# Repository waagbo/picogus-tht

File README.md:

# PicoGUS THT

PicoGUS is a Raspberry Pi Pico based ISA sound card for DOS and Win9x retro computers.
It is a highly versatile clone card that provides near perfect emulation of the Gravis Ultrasound, Sound Blaster-series, AdLib, Tandy 3-voice and CMS/Game Blaster.

Additional features like CD-ROM (Panasonic MKE), MPU-401 and USB game controllers build further on the cards versatility and the wavetable header will further extend the capacity with a card like [X2GS from Serdaco](https://serdashop.com/products/x2gs-te) to get the original Roland magic or even a [WavetablePi](https://github.com/scrapcomputing/WavetablePiHoriz) for the ultimate all-in-one experience for MS-DOS games. 

**PicoGUS THT is a through-hole conversion of the [PicoGUS project](https://github.com/polpo/picogus).**<br />
The conversion introduces through-hole components where possible in addition to embedding new features and ideas while still keeping the card compatible with the upstream project. The design goal is to make the project be easier to solder by hand as well as giving it a higher level of retro asthetics.

PicoGUS THT exists in multiple variants based on different PicoGUS revisions. Each variant is found in their separate folder (or branch if still experimental). The different *hw* designs feature additional documentation including ready to order BOM CSVs in their respective *docs* folders.

The designs still have some TSSOP SMD chips as they do not have THT equivalents, namely the two *SN74CB3T3257PWR* level shifters (U3/U4) as well as the PCM510xA DAC. PicoGUS THT features a redesigned footprint to ease debugging in case something goes wrong.

**Note!** The hardware revisions are intentionally kept aligned with the *major* revision as the original PicoGUS boards. This is done to indicate hardware feature compatibility and to prevent confusion in case of any future major revisions of the original PicoGUS design.

### Version 1.3

This version is an extension of the PicoGUS 1.2 design while implementing the *wavetable header* with manual volume control from the *hw-hand386* branch. Together with the addition of a full size USB-A connector accessible from the computers backside this card is now a real competitor to the v2.0 SMD design.

In addition, the THT boards have also been slightly resized to optimize for component placement and JCLPCB-pricing.
The v1.3.2 is currently under quality assurance. The following features have been tested and verified.
* [x] Card Assembly ➔ Minor adjustments to DigiKey BOM.
* [x] Flash, boot and detect card ➔ OK (v4.2.0-beta2).
* [x] Audio Playback ➔ OK (v4.2.0-beta2, SB Mode).
* [x] Wavetable MIDI Playback  ➔ OK (WavetablePi)
* [ ] External MIDI Playback
* [x] USB-A Connector (Both CD-ROM and experimental PGDFS filesystem)

The release version v1.3.2 is still pending build/test.

Assembly should be *EASY to MEDIUM* with the appropriate quality tools and consumables and a good project for beginners that want a little more challenge. Here is a list of recommended supplies with some personal recommendations:
* [Low Temperature Solder Paste](https://www.digikey.com/en/products/detail/chip-quik-inc/NC191LTA10/13531404) for easy soldering of SMD components.
* [Flux](https://www.digikey.com/en/products/detail/chip-quik-inc/NC191-2CC6/11480375) as it makes solder behave like magic when you need it the most.
* [Solder Wick](https://www.digikey.com/en/products/detail/chemtronics/SW14035/5177685) as it will help you when flux can't. Remember to **NEVER** pull a stuck wick.
* [Soldering Iron with J-Tip (Alientek T90B)](https://www.aliexpress.com/item/1005010015046346.html) will make the SMD components a breeze to solder. 
* [Tweezers](https://www.aliexpress.com/item/1005007298021096.html) for handling the SMD components.
* Digital Microscope of decent quality from AliExpress is very useful for visual inspection of SMD chips.
* Multimeter with good continuity tester.

### Version 2.1

This is an experimental extension of the PicoGUS 2.0 SMD design, made possible using a Waveshare Core2350B board to free enough I/O ports for the 2.0 feature set. This is still in the design phase.
<br/>

### Experimental Firmware
We have added experimental features that adds upon community ideas on top of the original firmware and software components. The features are submitted as Pull Requests to the original PicoGUS repository as well but there is no guarantee that they will ever be included in the official software releases:
* DFS drive support inspired by PicoMEM so the USB drive can be accessed from MS-DOS.
* CD images in a `CDROM` folder on the USB drive.
* A web page on boards with a Pico W or Pico 2 W: status, volumes, settings, mode switching, mt32-pi control and firmware updates from a browser.

The experimental features live on their own branches and are built into a separate *experimental* set of firmware and DOS tools next to the regular one, see [sw/experimental](sw/experimental/README.md).

### RP2350 Firmware
The firmware builds for the RP2350 as well as the RP2040, from the same source: for the v1.x boards with a Raspberry Pi Pico 2 (W) instead of a Pico (W), and for the v2.1 board's Core2350B module. Releases contain the firmware for both microcontrollers. See [RP2350 support](sw/docs/rp2350.md) for the firmware files, how to build them and what is left to test on hardware.

<br/>

**A big thank you to [Ian Scott (polpo)](https://github.com/polpo/) for the PicoGUS design and his contributions to the retro community.**<br/>**May his work set an example for future open-source hardware projects.**

--<br/>
Vidar Waagbø, Retro City AS

## PicoGUS

The original PicoGUS project is found at [polpo/pigocus](https://github.com/polpo/picogus) or www.picogus.com.<br/>
Here are the original README.md to give some more information about the great features of the PicoGUS:

ISA sound card and CD-ROM drive emulation on the Raspberry Pi Pico's RP2040 microcontroller. PicoGUS can emulate:

* [Gravis Ultrasound (GUS)](https://en.wikipedia.org/wiki/Gravis_Ultrasound) - the primary focus of PicoGUS, hence the name
* [Sound Blaster 16](https://en.wikipedia.org/wiki/Sound_Blaster_16) (OPL3) / [Sound Blaster Pro 2](https://en.wikipedia.org/wiki/Sound_Blaster#Sound_Blaster_Pro_2,_CT1600) (OPL3) / [AdLib](https://en.wikipedia.org/wiki/Ad_Lib,_Inc.) (OPL2)
* [MPU-401 (with intelligent mode)](https://en.wikipedia.org/wiki/MPU-401) - outputs MIDI data on 3.5mm MIDI TRS connector
* [Tandy 3-voice](http://www.vgmpf.com/Wiki/index.php?title=Tandy_3_Voice)
* [CMS/Game Blaster](http://nerdlypleasures.blogspot.com/2012/10/all-you-ever-wanted-to-know-about.html)
* [Game port joystick](https://en.wikipedia.org/wiki/Game_port)
* [Panasonic/MKE CD-ROM](https://en.wikipedia.org/wiki/Panasonic_CD_interface)

Current status: perpetual beta! See the [main wiki page](https://github.com/polpo/picogus/wiki) for current status and the [compatibility list](https://github.com/polpo/picogus/wiki/Compatibility-list) for support status of various DOS programs and other system compatibility notes. This project has a heavy demoscene focus due to the GUS's history so that's what I've concentrated on, but GUS support in games is very good to excellent.

Want to buy a PicoGUS? Fully assembled PicoGUS 2.0 sound cards are available from these sources, all of whom ship worldwide:

* [Joe's Computer Museum Shop](https://jcm-1.com/product/picogus-v2/) - in US 🇺🇸
* [Serdashop](https://www.serdashop.com/PicoGUS) - in EU 🇪🇺
* [Flamelily IT](https://shop.flamelily.co.uk/picogus) - in UK 🇬🇧

Want to make your own PicoGUS? See the [build guide](https://github.com/polpo/picogus/wiki/Building-your-PicoGUS). Note that the more DIY friendly v1.1.1 hardware has some documented issues with reset – a forthcoming v1.2 revision will fix these issues. **Important caveat**: due to the specs of the Pico, assumptions made by programs written to use the GUS, the imprecise nature of emulation, and the varying specs of retro DOS PC hardware, some things will likely never be perfect. **This is still a work in progress.**

Have a PicoGUS and want to use it? See the [configuring and using your PicoGUS guide](https://github.com/polpo/picogus/wiki/Configuring-and-using-your-PicoGUS).

Want to support PicoGUS? I have a limited number of machines to test PicoGUS in and donating either money or motherboards would be greatly appreciated and help increase the compatibility of PicoGUS.

You can donate via [PayPal](https://paypal.me/ianpolpo) or Ko-Fi: 

See/hear PicoGUS in action on YouTube:

Videos by others:

My videos:

## Open Source Credits

* [Raspberry Pi Pico C/C++ SDK](https://github.com/raspberrypi/pico-sdk)
* `pico_audio_i2s` from [pico-extras](https://github.com/raspberrypi/pico-extras)
* `stdio_async_uart` from [PicoCart64](https://github.com/kbeckmann/PicoCart64)
* `gus-x.cpp` adapted from [DOSBox-X](https://github.com/joncampbell123/dosbox-x)
* OPL/AdLib emulation from [rp2040-doom](https://github.com/kilograham/rp2040-doom) (based on [emu8950](https://github.com/digital-sound-antiques/emu8950))
* MPU-401 emulation adapted from [HardMPU](https://github.com/ab0tj/HardMPU) and [DOSBox-X](https://github.com/joncampbell123/dosbox-x)
* Tandy 3-voice emulation based on code contributed by [Aaron Giles](https://aarongiles.com/), adapted from [DREAMM](https://aarongiles.com/dreamm/) 
* CMS emulation based on code contributed by [Aaron Giles](https://aarongiles.com/), adapted from [DREAMM](https://aarongiles.com/dreamm/)
* USB support uses [TinyUSB](https://github.com/hathach/tinyusb) and [tusb_xinput](https://github.com/Ryzee119/tusb_xinput) with USB mass storage improvements by rppicomidi and wbcbz7.
* FAT drive support by [FatFS](https://elm-chan.org/fsw/ff/)

## License

The hardware portions of this repository (hw/ directory) are licensed under the CERN OHL version 2, permissive.

The software portions of this repository (sw/, pgusinit/ directories) as a collection are licensed under the GNU GPL version 2. Some files are individually dual-licensed under BSD or MIT licenses – see the license in the file headers for details.

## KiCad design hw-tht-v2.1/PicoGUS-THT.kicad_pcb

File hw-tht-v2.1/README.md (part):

# PicoGUS THT v2.1 – PicoGUS 2.0 in through hole, on a Waveshare Core2350B (RP2350B)

Board revision **v2.1**: the [PicoGUS 2.0](../hw-chipdown) circuit (chip-down RP2040, SMD) rebuilt for hand assembly
with through-hole parts. The RP2040, its flash, crystal and core regulator are replaced by a
**Waveshare Core2350B2** module (RP2350B, 16 MB flash, **8 MB PSRAM**) on four 2x8 sockets, and the module's PSRAM is
the GUS sample RAM, so v2.0's separate APS6404L is gone. Everything else is v2.0's circuit with the same GPIO map:
ISA bus logic, PCM5100A DAC, M62429 Waveblaster volume, MIDI out, USB-A host port and IRQ/DMA jumpers. The card is
the [THT v1.3.2](../hw-tht-v1.3/README.md) outline (102.0 × 99.95 mm), with v1.3.2's bracket-side connectors (USB-A,
line out, MIDI out) and bracket tab holes in v1.3.2's places, so the [v1.3.2 bracket](../hw-tht-v1.3/README.md#bracket) fits.
v2.0's passive line-out mix (four 1k resistors) is replaced by the **op-amp mixer of the THT v1.3 boards** (NE5532 on
ISA ±12 V, Waveblaster +6 dB), with film coupling capacitors and a DC-coupled DAC path.

An optional **Raspberry Pi Radio Module 2** (U14: the Pico W's Wi-Fi and Bluetooth radio) sits at the bracket end on
four of the module's free GPIOs, for the NE2000 (Wi-Fi) firmware: see [Radio module](#radio-module-optional).

**This branch (`hw2.1-tht-experimental`) adds an experimental boot ROM**: a 128 KB flash in a PLCC-32 socket (U15) and
a 74HCT138 address decoder (U16), enabled by one GPIO. **It is on the same 102.0 × 99.95 mm card**: the logic column
moved up 12.9 mm, the socket sits in the bottom left corner with the decoder on the back between its pins, and
that corner is routed with 0.15 mm tracks and clearances instead of 0.2 mm: see
[Boot ROM](#boot-rom-experimental). Without those parts the card works as the
plain v2.1.

The parts that only exist as SMD are soldered on the card: U1/U2 (SN74CB3T3257, TSSOP-16) and U10 (PCM5100A,
TSSOP-20) on THT v1.3.2's test-pad TSSOP footprints (hand-solder toes and a 0.7 mm test pad per pin), U13 (M62429L)
on v2.0's SOIC-8; the radio module is a castellated module on hand-solder lands. On this branch the boot ROM's
decoder U16 (74HCT138) is a TSSOP-16 too, **on the back of the card** between the pin rows of the flash socket, on
KiCad's standard TSSOP-16 lands (there is no room for test pads there): its DIP does not fit. Everything else is
through hole; see
[Parts with no through-hole version](#parts-with-no-through-hole-version).

> **Status: schematic done; board placed and routed (4 layers, DRC clean, matches the schematic), for review. Not
> built or tested. Firmware: ported and built (`picogus-v21.uf2`, and `pg-ne2k-v21.uf2` for the radio module), not tested on hardware** (see
> [Firmware](#firmware) and [Layout status](#layout-status)). The boot ROM of this branch is in the schematic and
> on the board (same checks), with a firmware switch for its enable pin; nothing of it is tested. JLCPCB files: `hw-common/tools/jlcpcb.sh
> hw-tht-v2.1/PicoGUS-THT.kicad_pcb` with `ALLOW_DRC=courtyards_overlap` (the 12 accepted overlaps in the logic
> column); the Hardware workflow builds them on every change.

Files:

| File | What |
|---|---|
| `PicoGUS-THT.kicad_pro/.kicad_sch/.kicad_pcb/.kicad_dru` | KiCad **10** project. Root sheet: v2.0's ISA logic, power, USB, Waveblaster and module |
| `audio.kicad_sch` | PCM5100A DAC sheet (v2.0's, footprints only) |
| `mixer.kicad_sch` | Line-out mixer: NE5532 inverting summing amplifier (from THT v1.3), ±12 V filters, Waveblaster input pull-downs |
| `bootrom.kicad_sch` | Experimental boot ROM: flash in a PLCC-32 socket, 74HCT138 decoder, base-address jumpers |
| `PicoGUS-THT-schematic.pdf` | Schematic PDF |
| `docs/BOM-THT.csv` | BOM with a **THT status** column (THT / THT but a different part than v2.0 / no THT version exists / module), the v2.0 part each line replaces, manufacturer, MPN, DigiKey and LCSC numbers, a digikey.no link, alternatives and digikey.no prices; then the kit items (module sockets and headers, jumpers), the optional IC sockets and the v2.0 parts that are gone |
| `docs/BOM-THT-digikey.csv` (+ `-optional`: the IC sockets) | DigiKey cart/BOM uploads (see [Cost](#cost)). Customer Reference `PicoGUS-THT-2.1.x: <references>` on every line, so the bags of a mixed order say which board they are for; at most 48 characters (DigiKey prints "Character Limit Exceeded" instead of a longer one), so the 15 × 0.1 µF line reads `C2-7,14-16,20,…` |
| `docs/BOM-THT-sockets.csv` | Optional: every IC socketed, with socket and part heights against the Waveblaster daughterboard. The same parts are the optional socket lines of `docs/BOM-THT.csv`, ordered with the `-optional` upload files |
| `docs/BOM-THT-lcsc-order.csv`, `docs/BOM-THT-lcsc.csv` (+ `-optional`) | The whole card from LCSC (see [Cost](#cost)): `-order` has every BOM line with the LCSC part, order quantity (LCSC minimums), stock and price on the day and what to buy elsewhere; the others are the uploads for LCSC's BOM tool, same customer references as the DigiKey ones |
| `tools/digikey_upload.py` | Writes both DigiKey upload files from `docs/BOM-THT.csv` (`python3 tools/digikey_upload.py [cards]`; more than one card gives `-<n>x` files) |
| `tools/lcsc_bom.py` | Writes the three LCSC files from `docs/BOM-THT.csv` with LCSC's live stock and prices (`python3 tools/lcsc_bom.py [cards]`) |
| `tools/gen_core2350b.py` | Generates the Core2350B footprint and 3D model in `hw-common` and checks the pin map |
| `tools/gen_rm2.py` | Generates the Radio Module 2 footprint and 3D model in `hw-common` and its symbol (dimensions from the RM2 datasheet) |
| `tools/gen_plcc32_socket.py` | Generates a simple 3D model of the PLCC-32 socket with its chip (`hw-common/parts/PLCC-32_THT-Socket.wrl`), for the renders: KiCad's library has none for that footprint |
| `docs/renders/` | 3D renders of the routed card: red from the front and the back, green, purple, white and black from the front (ENIG; white silkscreen, black on white). Made with `hw-common/tools/render.sh` |
| `docs/figures/routing.png` | The routed board: tracks per layer (In2.Cu carries part of the boot ROM's buses), vias and the AGND/AVDD islands |

The shared `PiGUS library` footprints are linked from `hw-common/`. **New in the shared library for v2.1:**
`Waveshare_Core2350B` (with a generated 3D model, `hw-common/parts/Waveshare_Core2350B.wrl`),
`RaspberryPi_RM2_HandSolder` (the Radio Module 2 with lands 1 mm past the module edge; 3D model
`hw-common/parts/RaspberryPi_RM2.wrl`),
`USB_C_Receptacle_GCT_USB4085`, `TSSOP-16_4.4x5mm_P0.65mm_HandSolder_TestPads` and
`TSSOP-20_4.4x6.5mm_P0.65mm_HandSolder_TestPads` (THT v1.3.2's: KiCad's TSSOP with the toes to ±3.9 mm and one
0.7 mm round test pad per pin in two staggered columns per side, at x ±4.45 / ±5.1 mm),
`USB_A_Molex_67643_Horizontal_ShieldPin5` (KiCad's Molex 67643 with the shield pads
numbered 5, as the `USB_A` symbol's shield pin) and `C_Film_P5.00mm_7.8x7.8mm_or_CP_D5.0mm_P2.00mm` (C39–C42).

## What changed compared to v2.0

The schematic is v2.0's (`hw-chipdown`), upgraded to KiCad 10 and edited. Its netlist was compared with v2.0's
connection by connection: apart from the changes in this table the two are identical (119 multi-pin nets each; the
radio module adds six to v2.1). Reference designators are v2.0's; new ones are D3, R19, R20, C46, the radio
module's U14, R33, R34 and C47, and the boot ROM's U15, U16, R35, C48, C49 and JP1–JP3.

| v2.0 | v2.1 | Why |
|---|---|---|
| U12 RP2040 (QFN-56), U11 W25Q128 flash, Y1 12 MHz crystal, R12/R14/R15/R16, C24–C37 (the RP2040 sheet) | **U12 Waveshare Core2350B** module on four 2x8 sockets (or soldered on its headers) | No chip-down RP2040 by hand. The module has the RP2350B, 16 MB flash, crystal, its own 3.3 V LDO and the 27 Ω USB resistors |
| U9 AMS1117-3.3 (SOT-223) | **U9 MCP1826S-3302E/AB** (TO-220) | Through hole, and 250 mV dropout: VSYS is now one Schottky drop below +5V (see [Power](#power)) |
| Q1 AO3401A ideal-diode switch (+5V → VSYS), R17 | **D3 1N5819** | No good TO-92 P-MOSFET; a second Schottky as for USB (D2) |
| J6 micro-USB (SMD) | **J6 GCT USB4085** through-hole USB-C + **R19/R20** 5.1 kΩ CC pull-downs, in v2.0's place on the bottom edge | Through hole; device only, never sources VBUS |
| – (no radio; the Pico-based boards take a Pico W) | **U14 Raspberry Pi Radio Module 2** (optional) + R33, R34, C47, on GPIO40/42/44/45 | Wi-Fi for the NE2000 firmware: see [Radio module](#radio-module-optional) |
| U6 74LVC2G06 (SOT-363), open-drain MIDI and I/O CH RDY drivers | **U6 74AHCT126** (DIP-14) on +5V + **C46** | No DIP open-drain inverter that runs on 3.3 V; the v1.3 THT boards' solution (OE = the old input, A tied low, so OE high pulls the line low). Spare gates tied low |
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
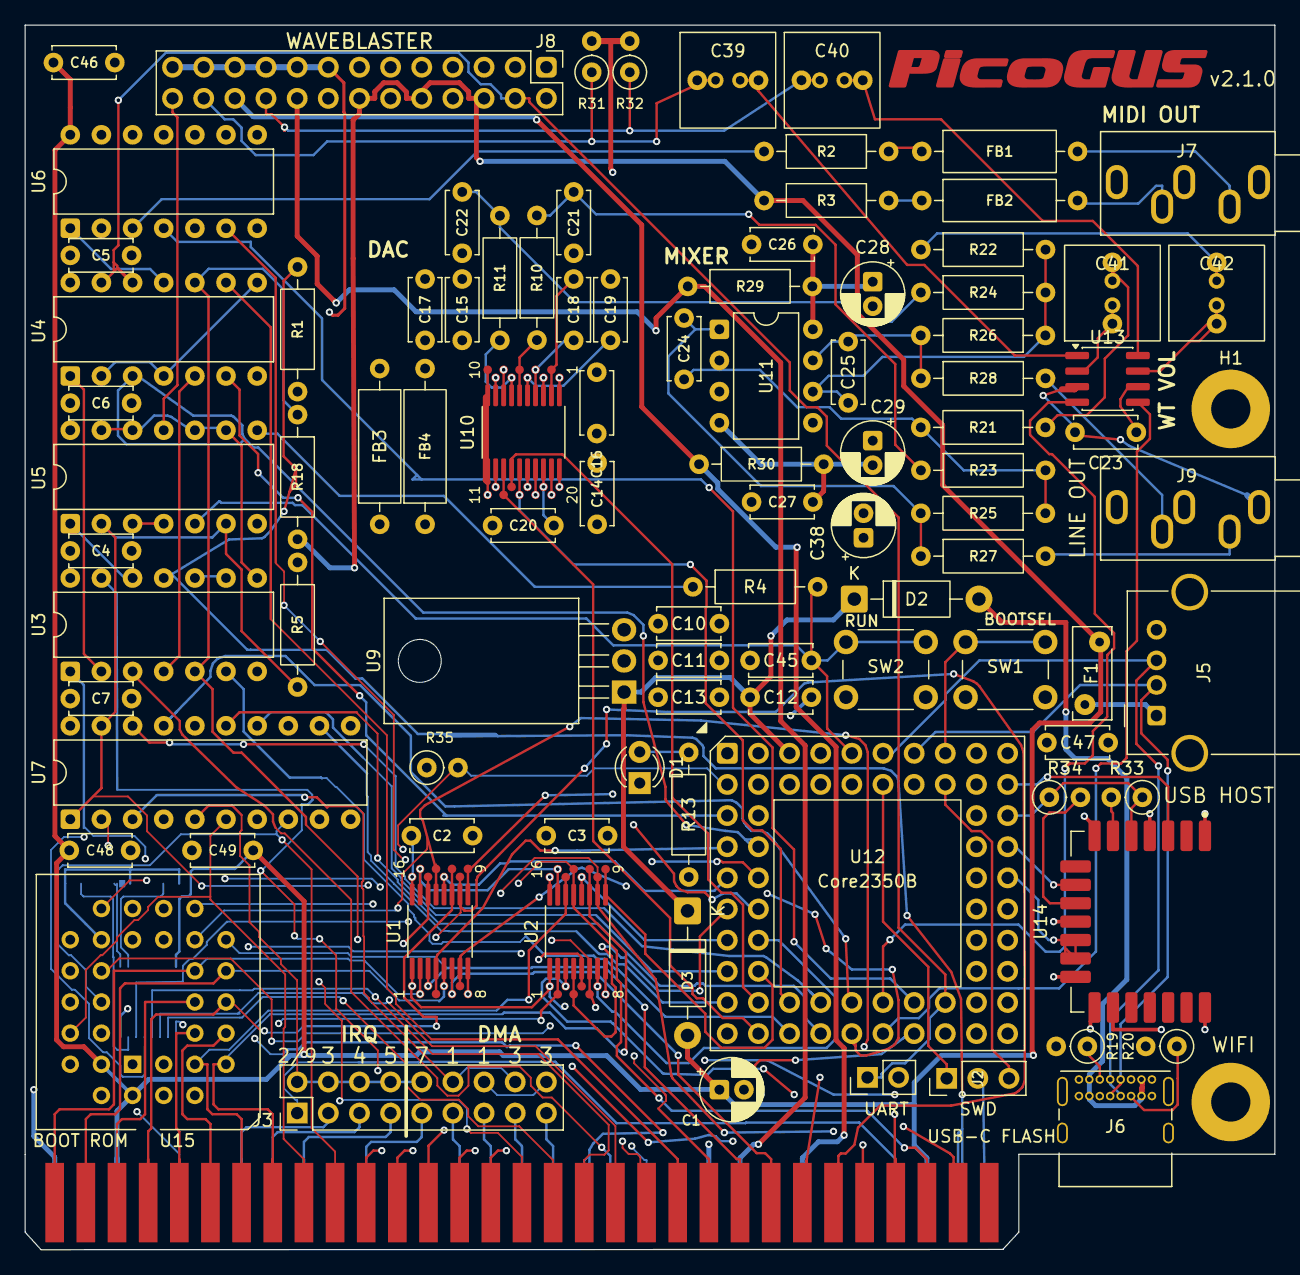
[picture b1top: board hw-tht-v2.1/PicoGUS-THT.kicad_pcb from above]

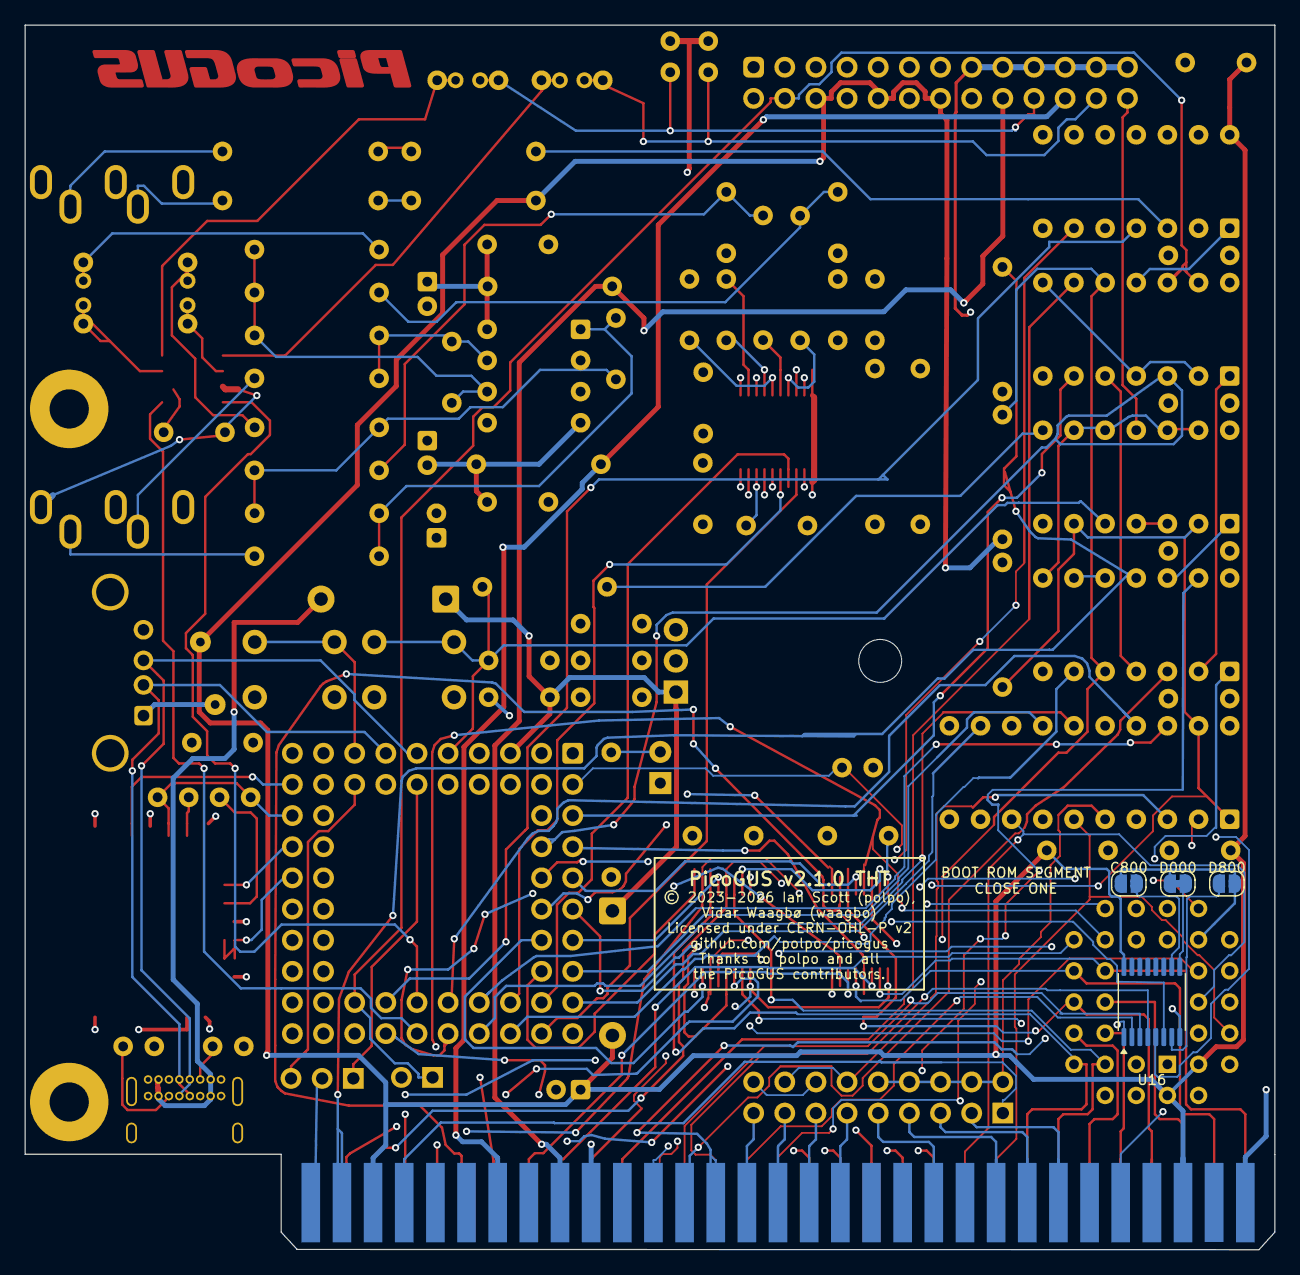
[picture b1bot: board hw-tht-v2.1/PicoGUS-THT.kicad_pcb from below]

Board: 4 copper layers, 101.9 x 99.8 mm, 102 parts (4 on the bottom side), 142 nets.

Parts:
C1, C28, C29: 47uF; CP_Radial_D5.0mm_P2.00mm
C2, C3, C4, C5, C6, C7, C14, C15, C16, C20, C23, C26, C27, C45, C46, C48, C49: 0.1uF; C_Disc_D5.0mm_W2.5mm_P5.00mm
C10: 1uF; C_Disc_D5.0mm_W2.5mm_P5.00mm
C11, C12, C13, C17, C47: 10uF; C_Disc_D5.0mm_W2.5mm_P5.00mm
C18, C19: 2.2uF; C_Disc_D5.0mm_W2.5mm_P5.00mm
C21, C22: 2.2nF; C_Disc_D5.0mm_W2.5mm_P5.00mm
C24, C25: 47pF C0G; C_Disc_D5.0mm_W2.5mm_P5.00mm
C38: 100uF; CP_Radial_D5.0mm_P2.00mm
C39, C40, C41, C42: 2.2uF film; C_Film_P5.00mm_7.8x7.8mm_or_CP_D5.0mm_P2.00mm
D1: LED; LED_D3.0mm
D2, D3: 1N5819; D_DO-41_SOD81_P10.16mm_Horizontal
F1: 0.5A PTC; Fuse_Bourns_MF-RHT050
FB1, FB2, FB3, FB4: Ferrite bead; R_Axial_DIN0309_L9.0mm_D3.2mm_P12.70mm_Horizontal
H1, H2: MountingHole; MountingHole_3.2mm_M3_Pad
J1: Bus_ISA_8bit; BUS_PC_chamfer
J2: SWD; PinHeader_1x03_P2.54mm_Vertical
J3: IRQ/DMA; PinHeader_2x09_P2.54mm_Vertical
J4: UART_TX; PinHeader_1x02_P2.54mm_Vertical
J5: USB-A host; USB_A_Molex_67643_Horizontal_ShieldPin5
J6: USB-C program; USB_C_Receptacle_GCT_USB4085
J7: SJ1-3535NG; Jack_3.5mm_CUI_SJ1-3535NG_Horizontal
J8: Waveblaster; Wavetable_NoMountingHoles
J9: SJ1-3535NG-GR; Jack_3.5mm_CUI_SJ1-3535NG_Horizontal
JP1, JP3: Open; SolderJumper-2_P1.3mm_Open_RoundedPad1.0x1.5mm
JP2: Bridged; SolderJumper-2_P1.3mm_Bridged_RoundedPad1.0x1.5mm
R1, R5, R21, R22: 10k; R_Axial_DIN0207_L6.3mm_D2.5mm_P10.16mm_Horizontal
R2, R3: 220R; R_Axial_DIN0207_L6.3mm_D2.5mm_P10.16mm_Horizontal
R4: 1k; R_Axial_DIN0207_L6.3mm_D2.5mm_P10.16mm_Horizontal
R10, R11, R13: 470R; R_Axial_DIN0207_L6.3mm_D2.5mm_P10.16mm_Horizontal
R18: 15k; R_Axial_DIN0207_L6.3mm_D2.5mm_P10.16mm_Horizontal
R19, R20: 5.1k; R_Axial_DIN0207_L6.3mm_D2.5mm_P2.54mm_Vertical
R23, R24, R25, R26: 20k; R_Axial_DIN0207_L6.3mm_D2.5mm_P10.16mm_Horizontal
R27, R28: 100R; R_Axial_DIN0207_L6.3mm_D2.5mm_P10.16mm_Horizontal
R29, R30: 10R; R_Axial_DIN0207_L6.3mm_D2.5mm_P10.16mm_Horizontal
R31, R32: 100k; R_Axial_DIN0207_L6.3mm_D2.5mm_P2.54mm_Vertical
R33: 470R; R_Axial_DIN0207_L6.3mm_D2.5mm_P2.54mm_Vertical
R34, R35: 10k; R_Axial_DIN0207_L6.3mm_D2.5mm_P2.54mm_Vertical
SW1: BOOTSEL; SW_PUSH_6mm
SW2: RUN; SW_PUSH_6mm
U1, U2: SN74CB3T3257; TSSOP-16_4.4x5mm_P0.65mm_HandSolder_TestPads
U3: 74AHC14; DIP-14_W7.62mm
U4, U5: 74AHC00; DIP-14_W7.62mm
U6: 74AHCT126; DIP-14_W7.62mm
U7: 74AHC244; DIP-20_W7.62mm
U9: MCP1826S-3302E/AB; TO-220-3_Horizontal_TabDown
U10: PCM5100A; TSSOP-20_4.4x6.5mm_P0.65mm_HandSolder_TestPads
U11: NE5532; DIP-8_W7.62mm
U12: Core2350B; Waveshare_Core2350B
U13: M62429L; SOIC-8_3.9x4.9mm_P1.27mm
U14: RM2; RaspberryPi_RM2_HandSolder
U15: SST39SF010A; PLCC-32_THT-Socket
U16: 74HCT138; TSSOP-16_4.4x5mm_P0.65mm

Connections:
+3V3: C2.1, C3.1, C4.1, C5.1, C6.1, C7.1, C10.1, C11.1, C13.1, C14.2, C47.1, FB4.1, R5.1, R35.1, U1.16, U2.16, U3.14, U4.14, U5.14, U7.20, U9.3, U10.17, U10.20, U14.14 (VDDIO), U14.16 (VIN)
+5V: C1.1, C46.1, C48.1, C49.1, D3.2, F1.2, J1.3, J1.29, J8.6, J8.10, J8.14, R3.2, R18.2, U6.14, U15.31, U15.32, U16.16
+12V: J1.9, J8.18, R29.1
-12V: J1.7, J8.22, R30.1
/Boot ROM/~CS_C8000: JP1.1, U16.10
/Boot ROM/~CS_D0000: JP2.1, U16.9
/Boot ROM/~CS_D8000: JP3.1, U16.7
/Boot ROM/~ROM_CS: JP1.2, JP2.2, JP3.2, U15.22
/Mixer/+12VA: C26.1, C28.1, R29.2, U11.8
/Mixer/-12VA: C27.2, C29.2, R30.2, U11.4
/Mixer/LINE_L: J9.T, R27.2
/Mixer/LINE_R: J9.R, R28.2
/Mixer/WTVOL_L: C41.2, R21.1
/Mixer/WTVOL_R: C42.2, R22.1
/USB_D+: J5.3, J6.A6, J6.B6, U12.25 (USB_DP)
/USB_D-: J5.2, J6.A7, J6.B7, U12.23 (USB_DM)
/VBUS_PRG: D2.2, J6.A4, J6.A9, J6.B4, J6.B9
/VSYS: C12.1, D2.1, D3.1, U9.1, U12.31 (VBUS)
/WL_CLK: U12.18 (GP45), U14.3 (SCLK)
/WL_CS: U12.61 (GP42), U14.9 (CS)
/WL_D: R33.1, R34.1, U12.63 (GP44), U14.5 (DATA_IN)
/WL_ON: U12.59 (GP40), U14.12 (WL_ON), U14.13 (BT_ON)
A0: J1.62, U1.2, U15.12
A1: J1.61, U1.5, U15.11
A2: J1.60, U1.14, U15.10
A3: J1.59, U1.11, U15.9
A4: J1.58, U2.2, U15.8
A5: J1.57, U2.5, U15.7
A6: J1.56, U2.14, U15.6
A7: J1.55, U2.11, U15.5
A8: J1.54, U7.6, U15.27
A9: J1.53, U7.8, U15.26
A10: J1.52, U15.23
A11: J1.51, U15.25
A12: J1.50, U15.4
A13: J1.49, U15.28
A14: J1.48, U15.29
A15: J1.47, U16.1
A16: J1.46, U16.2
A17: J1.45, U16.4
A18: J1.44, U16.3
A19: J1.43, U16.6
AD0: U1.4, U12.7 (GP6)
AD1: U1.7, U12.10 (GP7)
AD2: U1.12, U12.9 (GP8)
AD3: U1.9, U12.12 (GP9)
AD4: U2.4, U12.11 (GP10)
AD5: U2.7, U12.14 (GP11)
AD6: U2.12, U12.13 (GP12)
AD7: U2.9, U12.16 (GP13)
ADS: U1.1, U2.1, U3.13, U12.45 (GP27)
AEN: J1.42, U4.9
AGND: C15.1, C16.1, C17.2, C19.2, C21.1, C22.1, C23.2, C26.2, C27.1, C28.2, C29.1, C38.2, FB3.2, J8.15, J8.17, J8.19, J8.21, J8.23, J8.25, J9.S, R31.2, R32.2, U10.3, U10.9, U11.3, U11.5, U13.3
AVDD: C15.2, C16.2, C17.1, C23.1, C38.1, FB4.2, U10.1, U10.8, U13.6
BCK: U10.13, U12.35 (GP17)
D0: J1.40, U1.3, U15.13
D1: J1.39, U1.6, U15.14
D2: J1.38, U1.13, U15.15
D3: J1.37, U1.10, U15.17
D4: J1.36, U2.3, U15.18
D5: J1.35, U2.6, U15.19
D6: J1.34, U2.13, U15.20
D7: J1.33, U2.10, U15.21
DACK: J3.14, J3.18, R18.1, U3.5, U4.10
DACK1: J1.17, J3.13
DACK3: J1.15, J3.17
DIN: U10.14, U12.36 (GP16)
DRQ: J3.12, J3.16, U7.3
DRQ1: J1.18, J3.11
DRQ3: J1.16, J3.15
GND: C1.2, C2.2, C3.2, C4.2, C5.2, C6.2, C7.2, C10.2, C11.2, C12.2, C13.2, C14.1, C20.2, C45.2, C46.2, C47.2, C48.2, C49.2, D1.1, FB3.1, H1.1, H2.1, J1.1, J1.10, J1.31, J2.2, J4.2, J5.4, J5.5, J6.A1, J6.A12, J6.B1, J6.B12, J6.SH, J7.S, J8.1, J8.3, J8.5, J8.7, J8.9, J8.11, R1.2, R19.2, R20.2, SW1.2, SW2.2, U1.8, U2.8, U3.7, U4.7, U5.7, U6.2, U6.5, U6.7, U6.9, U6.10, U6.12, U6.13, U7.4, U7.10, U7.11, U7.13, U9.2, U10.10, U10.11, U10.12, U10.16, U10.19, U12.1 (GND), U12.17 (GND), U12.24 (GND), U12.30 (GND), U12.33 (GND), U12.47 (GP29), U12.49 (GND), U14.1 (GND), U14.4 (GND), U14.7 (GND), U14.11 (GND), U14.15 (GND), U14.21 (GND), U15.2, U15.3, U15.16, U16.8
IRQ: J3.2, J3.4, J3.6, J3.8, J3.10, U7.5
IRQ2: J1.4, J3.1
IRQ3: J1.25, J3.3
IRQ4: J1.24, J3.5
IRQ5: J1.23, J3.7
IRQ7: J1.21, J3.9
I/OCHRDY: J1.41, U6.6
LRCK: U10.15, U12.38 (GP18)
unnamed: C24.2, R25.2, R27.1, U11.1
unnamed: C25.2, R26.2, R28.1, U11.7
unnamed: D1.2, R13.2
unnamed: FB1.1, R2.2
unnamed: FB1.2, J7.T
unnamed: FB2.1, R3.1
unnamed: FB2.2, J7.R
unnamed: J2.1, U12.26 (SWCLK)
unnamed: J2.3, U12.22 (SWDIO)
unnamed: F1.1, J5.1
unnamed: J6.A5, R19.1
unnamed: J6.B5, R20.1
unnamed: R2.1, U6.3
unnamed: R4.1, U5.8
unnamed: U3.2, U4.1
unnamed: U3.4, U4.5
unnamed: U3.8, U5.9, U5.10, U5.12, U5.13
unnamed: U3.9, U3.10
unnamed: U3.12, U5.1
unnamed: U4.2, U4.4, U4.8
unnamed: U4.11, U6.1
unnamed: U5.3, U5.4
unnamed: C18.2, U10.4
unnamed: C18.1, U10.2
unnamed: C20.1, U10.18
unnamed: R10.1, U10.6
unnamed: R11.1, U10.7
unnamed: C19.1, U10.5
unnamed: C24.1, R21.2, R23.2, R25.1, U11.2
unnamed: C25.1, R22.2, R24.2, R26.1, U11.6
unnamed: SW1.1, U12.21 (BOOTSEL)
unnamed: R13.1, U12.41 (GP23)
unnamed: C39.2, U13.1
unnamed: C41.1, U13.2
unnamed: C40.2, U13.8
unnamed: C42.1, U13.7
unnamed: R33.2, U14.6 (DATA_OUT)
unnamed: R34.2, U14.10 (nIRQ)
PGAUDIO_L: C21.2, R10.2, R23.1
PGAUDIO_R: C22.2, R11.2, R24.1
RA8: U7.14, U12.15 (GP14)
RA9: U7.12, U12.34 (GP15)
RDRQ: U7.17, U12.42 (GP22)
RESET: J1.2, R1.1, U3.11
RIRQ: U7.15, U12.39 (GP21)
RI/OCHRDY: U6.4, U12.46 (GP26)
RTC: U7.18, U12.40 (GP20)
RUN: C45.1, R4.2, SW2.1, U5.5, U12.27 (RUN)
RV_CLK: U12.43 (GP25), U13.5
RV_DATA: U12.44 (GP24), U13.4
TC: J1.27, U7.2
UART_TX: J4.1, J8.4, U4.12, U4.13, U12.48 (GP28)
WTAUDIO_L: C39.1, J8.24, R31.1
WTAUDIO_R: C40.1, J8.20, R32.1
~BUSOE: R5.2, U1.15, U2.15, U5.2, U5.6, U7.1, U7.19
~IOR: J1.14, U3.1
~IOW: J1.13, U3.3
~RDACK: U3.6, U12.37 (GP19)
~RIOR: U4.3, U12.8 (GP5)
~RIOW: U4.6, U12.5 (GP4)
~ROM_EN: R35.2, U12.3 (GP2), U16.5
~SMEMR: J1.12, U15.24
~WT_RESET: J8.26, U5.11

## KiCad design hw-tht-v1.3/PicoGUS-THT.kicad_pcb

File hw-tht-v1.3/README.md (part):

# PicoGUS THT (through-hole) v1.3.2 – based on PicoGUS v1.2

Board revision **v1.3.2**: the v1.3.1 (rev B) THT board on a 102 mm outline, with
the fine-pitch chips soldered straight to the card and a test pad on every one of their pins.

* **U3/U4** (SN74CB3T3257, TSSOP-16) and **U9** (PCM5100A, TSSOP-20; the PCM5101A/5102A fit too) only exist as TSSOPs. They are soldered to
  the card on hand-solder footprints, and **every pin has its own 0.7 mm round test pad** in line with it, for a
  probe, a meter or a scope (see [U3/U4 and U9 with a test pad per pin](#u3u4-and-u9-with-a-test-pad-per-pin)).
  The TSSOP-to-DIP adapter boards of the earlier v1.3.2 layout are gone, and so are their sockets.
* **The GY-PCM5102 module option (J10) is gone.** The on-board DAC is always fitted.
* **New placement** of the DAC block, the mixer and the jacks (2026-10-31 / 2026-11-01): the DAC sits above U3/U4
  with its analog side facing east toward the output filter and the mixer above it, MIDI OUT at the top of the
  bracket end and LINE OUT below WT VOL (see [Placement](#placement)).
* **C36** (U9 charge-pump decoupling) is a through-hole 0.1 µF disc, and all eight DAC decoupling discs sit on the
  side of U9 where their pins are (see [DAC decoupling](#dac-decoupling)).
* **C8/C10** (U8 PSRAM decoupling) are the v1.3.1 through-hole discs, next to U8.
* **1.84 mm shorter**: 102.0 mm long over the outline (v1.3.1: 103.8 mm), trimmed at the bracket end. The bracket tab
  holes H1/H2 are 1.70 mm further from the bracket plate, so the card needs a bracket with longer tabs (see
  [Bracket](#bracket)).
* **No artwork on the back silkscreen**: the princess artwork is to be UV printed instead. The back texts stay.

The main board is through-hole apart from **U3, U4, U9** (TSSOP, 0.65 mm pitch), **U8** (APS6404L PSRAM, SOIC-8,
1.27 mm pitch) and the optional **U12** (USBLC6-2SC6, SOT-23-6), all on the front. The rest of the circuit is
v1.3.1's: USB-A host port, Waveblaster header, op-amp mixer.

> **Status: v1.3.2, ready to order (tag `v1.3.2-tht`); not built or tested yet.** The placement of 2026-11-01 is
> routed on two layers (2026-11-01).
> The schematic's ERC is the same as v1.3.1's (280 warnings, 0 errors). DRC with schematic parity finds 0
> unconnected items and, as errors, only the 12 accepted courtyard overlaps in the logic column, so
> `hw-common/tools/jlcpcb.sh` exports with `ALLOW_DRC=courtyards_overlap`; `build/jlcpcb/` holds that export (not in git: the repository
> ignores `build/`). The first routed TSSOP layout (commit 298e993) was reviewed independently; this placement
> shortens the DAC outputs and the mixer's summing nodes that review pointed at, and its route applies the review's
> rules from the start. Compared with the routed DIP-adapter layout (commit d5c4a85) it is better on I2S, the
> DAC-to-mixer path and the vias at silkscreen text, and worse on the ISA data-bus length, which the test pads set:
> see [Layout status](#layout-status).

Files:

| File | What |
|---|---|
| `PicoGUS-THT.kicad_pro/.kicad_sch/.kicad_pcb` | KiCad **10** project (the root sheet is the v1.2 logic). The board is routed |
| `audio.kicad_sch` | PCM510x DAC sheet: U9 a TSSOP-20 with test pads, C36 a THT disc, no J10 |
| `wavetable.kicad_sch` | Waveblaster header, WT volume, op-amp mixer, line-out jack (as v1.3.1) |
| `usb.kicad_sch` | USB host port (J11 USB-A, F1, C34/C35, U12) (as v1.3.1) |
| `PicoGUS-THT-schematic.pdf` | Schematic PDF |
| `docs/BOM-THT.csv` | BOM with DigiKey **and** LCSC part numbers, stock (2026-11-07) and a digikey.no link per line |
| `docs/BOM-THT-digikey.csv`, `-lcsc.csv`, `-mouser.csv` | DigiKey, LCSC and Mouser upload files for one board, made from `BOM-THT.csv` (see [Ordering](#ordering)); the optional parts (sockets, U12) are at the bottom, marked "(optional)" |
| `docs/renders/` | 3D renders of the routed card: red from the front and the back, green, purple, white and black from the front (ENIG; white silkscreen, black on white). Made with `hw-common/tools/render.sh` |
| `docs/figures/` | Figures for the README's exceptions and design choices (e.g. the test pads, the placement options, the accepted courtyard overlaps), with the scripts that make them in `docs/figures/src/` |

The shared `PiGUS library` symbols and footprints are linked from `hw-common/`, like the other boards. **New in the
shared library for v1.3.2:** `TSSOP-16_4.4x5mm_P0.65mm_HandSolder_TestPads` (U3, U4),
`TSSOP-20_4.4x6.5mm_P0.65mm_HandSolder_TestPads` (U9) and `RPi_Pico_SMD_TH_USB_NoSWD` (U1, see
[102 mm board](#102-mm-board)), in `hw-common/PiGUS library.pretty`; DRC's library check finds the board's U1, U3,
U4 and U9 identical to them. The adapter footprints and adapter 3D models of the earlier v1.3.2 layout are removed;
the older `DIP-16_W7.62mm_TSSOP-16_Nested` stays unused.

Every part has a 3D model. The ones KiCad 10's library does not have are in `hw-common/parts`, reached through the
project folder's `parts` link: the CUI SJ1-3535NG jacks (J8 green; J5 a black copy of the same CUI model), the Alps
RK09712 pot (RV1) and a simple generated Bourns MF-R050 (F1). U3/U4/U9 use KiCad's TSSOP models, U1 KiCad's own
`RaspberryPi_Pico.step`, and J9's header model path is fixed. The library footprints carry the same models as the
board.

## What changed compared to v1.3.1

### U3/U4 and U9 with a test pad per pin

| | U3, U4 (SN74CB3T3257, TSSOP-16) | U9 (PCM5100A, TSSOP-20) |
|---|---|---|
| Footprint | `PiGUS library:TSSOP-16_4.4x5mm_P0.65mm_HandSolder_TestPads` | `PiGUS library:TSSOP-20_4.4x6.5mm_P0.65mm_HandSolder_TestPads` |
| Courtyard | 11.4 × 5.75 mm | 11.4 × 7.05 mm |
| Position (centre) | U3 (150.22, 110.10), U4 (161.44, 110.12), both 90° (pin 1 at the bottom left) | (156.10, 84.53), 180° (pin 1 at the bottom right) |

* **Land pattern**: the TSSOP hand-solder pads (1.775 × 0.40 mm at ±3.01 mm from the centre, toes out to ±3.9 mm),
  long enough to put an iron on each pin.
* **One test pad per pin**: a 0.7 mm round pad (bare copper, `testpoint` property) straight out from each pin,
  joined to it by a 0.2 mm track. The pads alternate between two columns, 4.45 and 5.10 mm from the centre, so each
  sits on its own pin's line and 1.3 mm from the next pad in its column; the track to an outer pad passes between two
  inner pads with 0.2 mm on each side, the board's normal clearance. The footprint has the pin numbers at the column
  ends in 0.8 mm silk. The pads make every pin reachable for a probe, a meter or a scope clip, and a solder bridge
  between two pins shows up as a short between their pads.
* **Routing**: an outer-column pin is routed from its test pad. An inner-column pin that is used gets a 0.2 mm
  escape stub straight on from its test pad, centred between the two outer pads, to 5.80 mm from the centre, and is
  routed from the stub end (26 stubs; the two left unused are removed after routing, see
  [Layout status](#layout-status)). The router cannot squeeze a track between two outer pads (0.6 mm
  gap) any other way, and the stubs keep the 0.2 mm clearance exactly as the pin-to-pad tracks do.
* **Pin numbers stay the schematic's**: U9 is 1 CPVDD, 2 CAPP, 3 CPGND, 4 CAPM, 5 VNEG, 6 OUTL, 7 OUTR, 8 AVDD,
  9 AGND, 10 DEMP, 11 FLT, 12 SCK, 13 BCK, 14 DIN, 15 LRCK, 16 FMT, 17 XSMT, 18 LDOO, 19 DGND, 20 DVDD.
* The symbols' `Adapter` fields and the adapter wording in the descriptions and sheet notes are gone; the root sheet
  says "SMD: U3/U4 TSSOP-16, U9 TSSOP-20 (with test pads), U8 SOIC-8, U12 opt.".

![Test pads on U9 (and U3/U4): the TSSOP-20 land pattern to scale with its 20 test pads in two staggered columns
(inner 4.45 mm, outer 5.10 mm from the centre, 1.3 mm between two pads of a column), the 0.2 mm track from each pin
to its pad passing between two pads with 0.2 mm clearance on each side, and the escape stubs that carry an
inner-column pin out between two outer pads to the routing](docs/figures/test-pads.png)

### No GY-PCM5102 module option

J10 (the GY-PCM5102 module, soldered on male pins over the DAC area as the alternative to the on-board DAC since
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
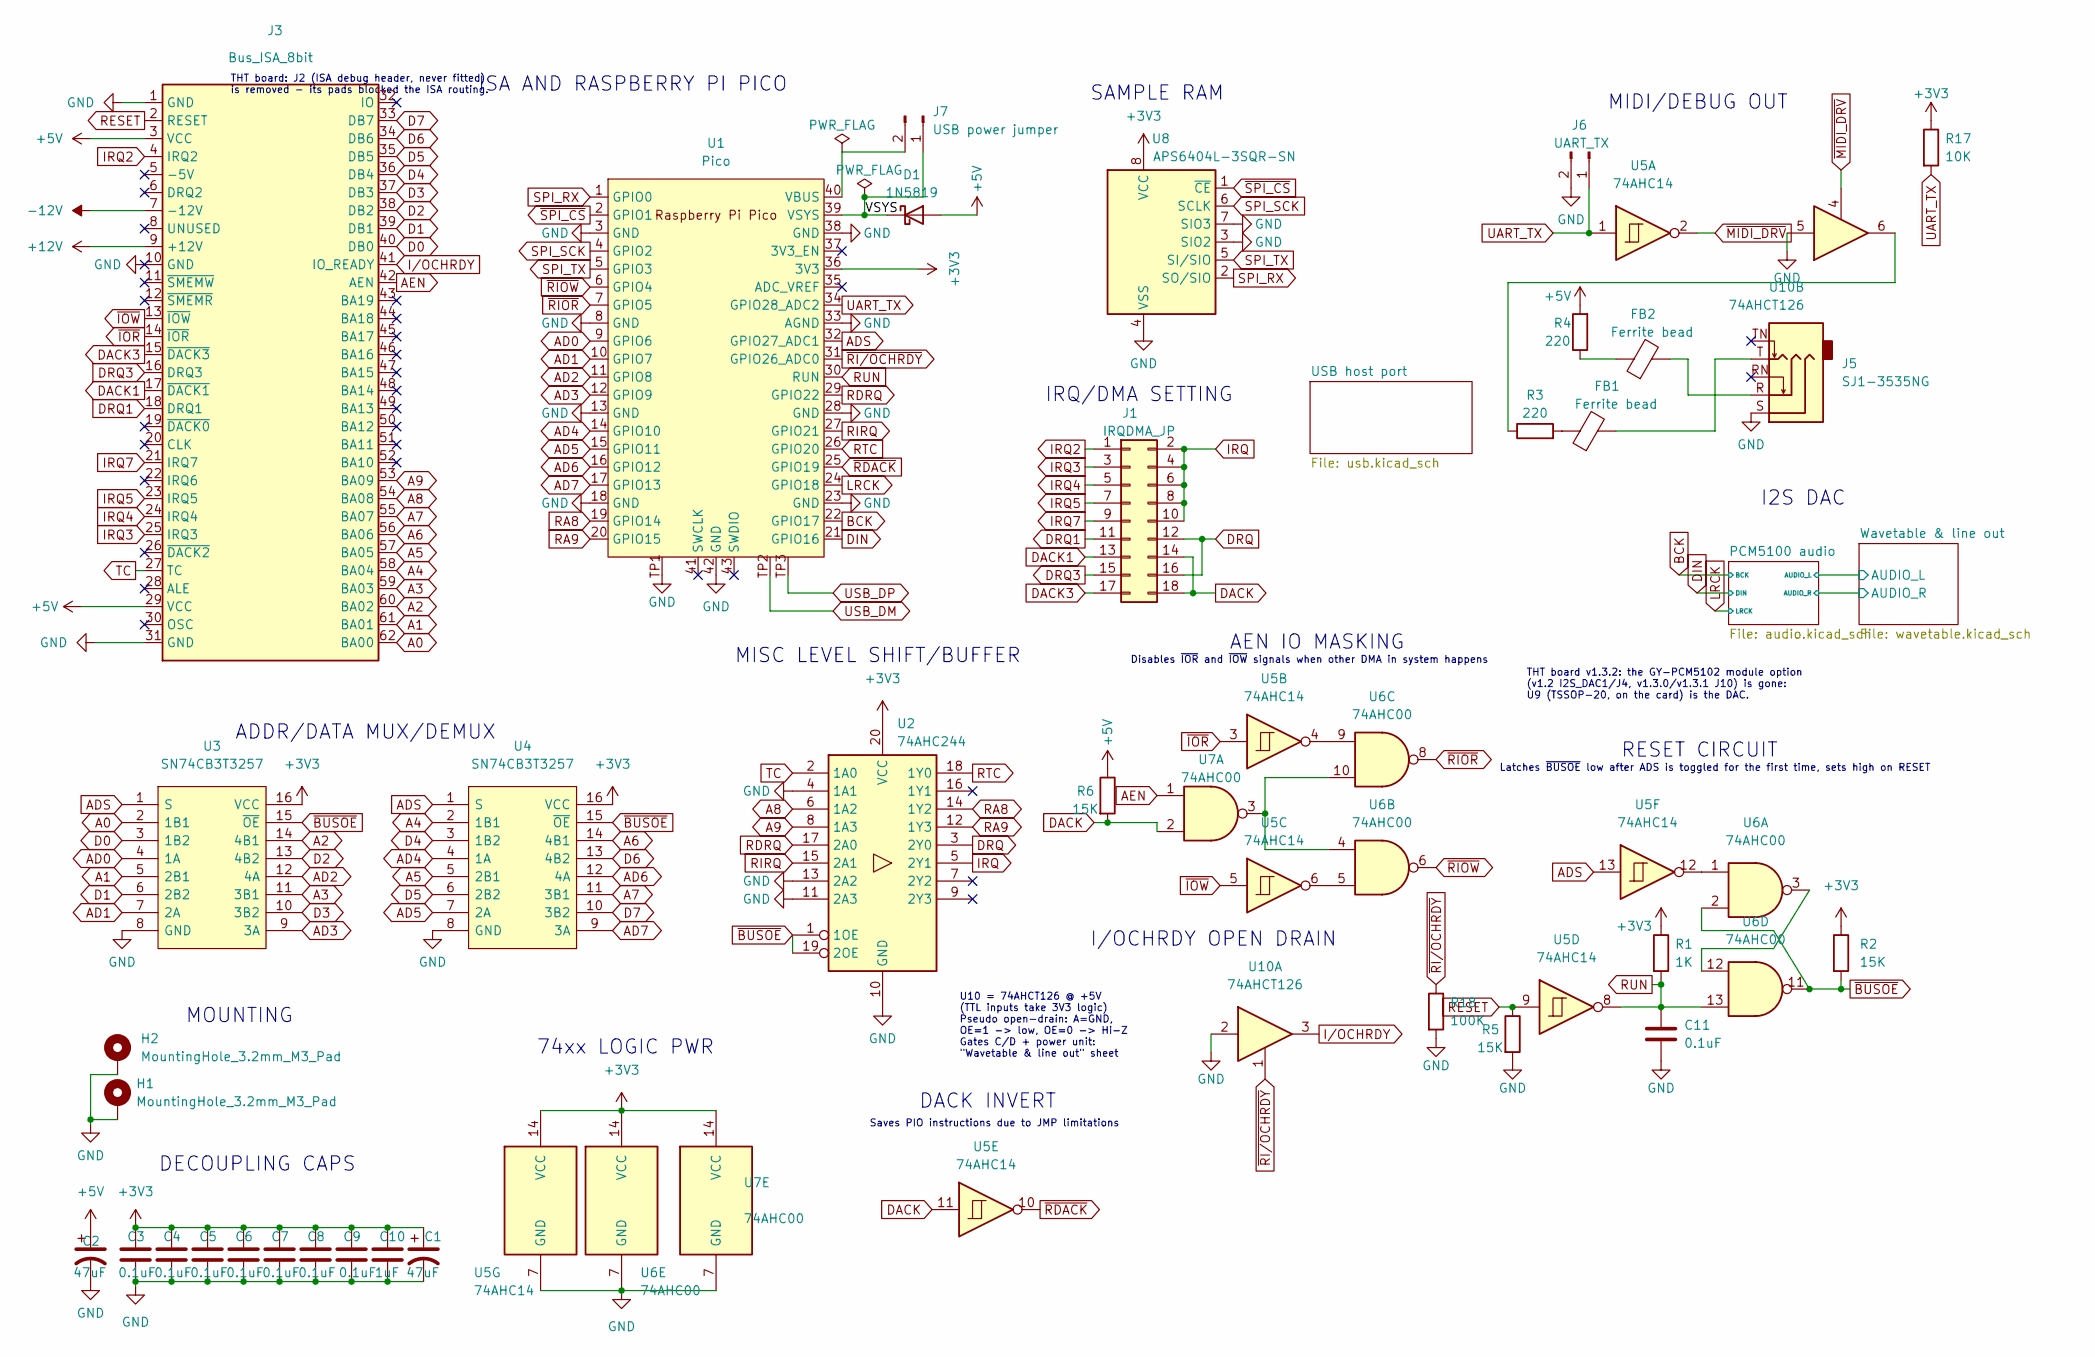
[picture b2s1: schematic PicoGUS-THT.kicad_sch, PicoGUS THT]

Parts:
C1, C2: 47uF; CP_Radial_D5.0mm_P2.00mm; MPN 35YXJ47M5X11; DigiKey 1189-2919-ND
C3, C4, C5, C6, C7, C8, C9, C11: 0.1uF; C_Disc_D5.0mm_W2.5mm_P5.00mm; MPN RDER71H104K0M1H03A; DigiKey 490-9144-1-ND
C10: 1uF; C_Disc_D5.0mm_W2.5mm_P5.00mm; MPN RDER71H105K2M1H03A; DigiKey 490-9146-1-ND
D1: 1N5819; D_DO-41_SOD81_P10.16mm_Horizontal; MPN 1N5819RLG; DigiKey 1N5819RLGOSCT-ND
FB1, FB2: Ferrite bead; R_Axial_DIN0309_L9.0mm_D3.2mm_P12.70mm_Horizontal; MPN 2743002112; DigiKey 1934-1477-1-ND
H1, H2: MountingHole_3.2mm_M3_Pad
J1: IRQDMA_JP; PinHeader_2x09_P2.54mm_Vertical; MPN 77313-118-18LF; DigiKey 609-77313-118-18LF-ND
J3: Bus_ISA_8bit; BUS_PC_chamfer
J5: SJ1-3535NG; Jack_3.5mm_CUI_SJ1-3535NG_Horizontal; MPN SJ1-3535NG; DigiKey CP1-3535NG-ND
J6: UART_TX; PinHeader_1x02_P2.54mm_Vertical; MPN 77311-118-02LF; DigiKey 609-4434-ND
J7: USB power jumper; PinHeader_1x02_P2.54mm_Vertical; MPN 77311-118-02LF; DigiKey 609-4434-ND
R1: 1K; R_Axial_DIN0207_L6.3mm_D2.5mm_P10.16mm_Horizontal; MPN MFR-25FBF52-1K; DigiKey 1.00KXBK-ND
R2, R5, R6: 15K; R_Axial_DIN0207_L6.3mm_D2.5mm_P10.16mm_Horizontal; MPN MFR-25FBF52-15K; DigiKey 15.0KXBK-ND
R3, R4: 220; R_Axial_DIN0207_L6.3mm_D2.5mm_P10.16mm_Horizontal; MPN RNMF14FTC220R; DigiKey S220CACT-ND
R17: 10K; R_Axial_DIN0207_L6.3mm_D2.5mm_P10.16mm_Horizontal; MPN MFR-25FBF52-10K; DigiKey 10.0KXBK-ND
R18: 100K; R_Axial_DIN0207_L6.3mm_D2.5mm_P10.16mm_Horizontal; MPN MFR-25FBF52-100K; DigiKey 100KXBK-ND
U1: Pico; RPi_Pico_SMD_TH_USB_NoSWD; MPN SC0915; DigiKey 2648-SC0915CT-ND
U2: 74AHC244; DIP-20_W7.62mm; MPN SN74AHC244N; DigiKey 296-4585-5-ND
U3, U4: SN74CB3T3257; TSSOP-16_4.4x5mm_P0.65mm_HandSolder_TestPads; MPN SN74CB3T3257PWR; DigiKey 296-17850-1-ND
U5: 74AHC14; DIP-14_W7.62mm; MPN SN74AHC14N; DigiKey 296-4550-5-ND
U6, U7: 74AHC00; DIP-14_W7.62mm; MPN SN74AHC00N; DigiKey 296-4510-5-ND
U8: APS6404L-3SQR-SN; SOIC-8_3.9x4.9mm_P1.27mm; MPN APS6404L-3SQR-SN; DigiKey 1528-4677-ND (Adafruit 4677 (64Mbit QSP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
U10: 74AHCT126; DIP-14_W7.62mm; MPN SN74AHCT126N; DigiKey 296-4659-5-ND

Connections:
+3V3: C1.1, C3.1, C4.1, C5.1, C6.1, C7.1, C8.1, C9.1, C10.1, R1.1, R2.1, R17.1, U1.36 (3V3), U2.20 (VCC), U3.16 (VCC), U4.16 (VCC), U5.14 (VCC), U6.14 (VCC), U7.14 (VCC), U8.8 (VCC); also elsewhere on the board
+5V: C2.1, D1.2 (A), J3.3 (VCC), J3.29 (VCC), R4.2, R6.1; also elsewhere on the board
+12V: J3.9 (+12V); also elsewhere on the board
-12V: J3.7 (-12V); also elsewhere on the board
/VSYS: D1.1 (K), J7.1, U1.39 (VSYS)
A0: J3.62 (BA00), U3.2 (1B1)
A1: J3.61 (BA01), U3.5 (2B1)
A2: J3.60 (BA02), U3.14 (4B1)
A3: J3.59 (BA03), U3.11 (3B1)
A4: J3.58 (BA04), U4.2 (1B1)
A5: J3.57 (BA05), U4.5 (2B1)
A6: J3.56 (BA06), U4.14 (4B1)
A7: J3.55 (BA07), U4.11 (3B1)
A8: J3.54 (BA08), U2.6 (1A2)
A9: J3.53 (BA09), U2.8 (1A3)
AD0: U1.9 (GPIO6), U3.4 (1A)
AD1: U1.10 (GPIO7), U3.7 (2A)
AD2: U1.11 (GPIO8), U3.12 (4A)
AD3: U1.12 (GPIO9), U3.9 (3A)
AD4: U1.14 (GPIO10), U4.4 (1A)
AD5: U1.15 (GPIO11), U4.7 (2A)
AD6: U1.16 (GPIO12), U4.12 (4A)
AD7: U1.17 (GPIO13), U4.9 (3A)
ADS: U1.32 (GPIO27_ADC1), U3.1 (S), U4.1 (S), U5.13
AEN: J3.42 (AEN), U7.1
BCK: U1.22 (GPIO17); also elsewhere on the board
D0: J3.40 (DB0), U3.3 (1B2)
D1: J3.39 (DB1), U3.6 (2B2)
D2: J3.38 (DB2), U3.13 (4B2)
D3: J3.37 (DB3), U3.10 (3B2)
D4: J3.36 (DB4), U4.3 (1B2)
D5: J3.35 (DB5), U4.6 (2B2)
D6: J3.34 (DB6), U4.13 (4B2)
D7: J3.33 (DB7), U4.10 (3B2)
DACK: J1.14, J1.18, R6.2, U5.11, U7.2
DACK1: J1.13, J3.17 (~DACK1)
DACK3: J1.17, J3.15 (~DACK3)
DIN: U1.21 (GPIO16); also elsewhere on the board
DRQ: J1.12, J1.16, U2.3 (2Y0)
DRQ1: J1.11, J3.18 (DRQ1)
DRQ3: J1.15, J3.16 (DRQ3)
GND: C1.2, C2.2, C3.2, C4.2, C5.2, C6.2, C7.2, C8.2, C9.2, C10.2, C11.2, H1.1, H2.1, J3.1 (GND), J3.10 (GND), J3.31 (GND), J5.S, J6.2, R5.2, R18.2, U1.3 (GND), U1.8 (GND), U1.13 (GND), U1.18 (GND), U1.23 (GND), U1.28 (GND), U1.33 (AGND), U1.38 (GND), U1.42 (GND), U1.TP1, U2.4 (1A1), U2.10 (GND), U2.11 (2A3), U2.13 (2A2), U3.8 (GND), U4.8 (GND), U5.7 (GND), U6.7 (GND), U7.7 (GND), U8.3 (SIO2), U8.4 (VSS), U8.7 (SIO3), U10.2, U10.5; also elsewhere on the board
IRQ: J1.2, J1.4, J1.6, J1.8, J1.10, U2.5 (2Y1)
IRQ2: J1.1, J3.4 (IRQ2)
IRQ3: J1.3, J3.25 (IRQ3)
IRQ4: J1.5, J3.24 (IRQ4)
IRQ5: J1.7, J3.23 (IRQ5)
IRQ7: J1.9, J3.21 (IRQ7)
I/OCHRDY: J3.41 (IO_READY), U10.3
LRCK: U1.24 (GPIO18); also elsewhere on the board
unnamed: FB1.1, R3.2
unnamed: FB1.2, J5.T
unnamed: FB2.1, R4.1
unnamed: FB2.2, J5.R
unnamed: J7.2, U1.40 (VBUS)
unnamed: R3.1, U10.6
unnamed: U5.4, U6.9
unnamed: U5.6, U6.5
unnamed: U5.12, U6.1
unnamed: U6.4, U6.10, U7.3
unnamed: U6.3, U6.12
RA8: U1.19 (GPIO14), U2.14 (1Y2)
RA9: U1.20 (GPIO15), U2.12 (1Y3)
RDRQ: U1.29 (GPIO22), U2.17 (2A0)
RESET: J3.2 (RESET), R5.1, U5.9; also elsewhere on the board
RIRQ: U1.27 (GPIO21), U2.15 (2A1)
RTC: U1.26 (GPIO20), U2.18 (1Y0)
RUN: C11.1, R1.2, U1.30 (RUN), U5.8, U6.13
SPI_RX: U1.1 (GPIO0), U8.2 (SO/SIO)
SPI_SCK: U1.4 (GPIO2), U8.6 (SCLK)
SPI_TX: U1.5 (GPIO3), U8.5 (SI/SIO)
TC: J3.27 (TC), U2.2 (1A0)
UART_TX: J6.1, R17.2, U1.34 (GPIO28_ADC2), U5.1
USB_DM: U1.TP2; also elsewhere on the board
USB_DP: U1.TP3; also elsewhere on the board
~BUSOE: R2.2, U2.1 (1OE), U2.19 (2OE), U3.15 (~OE), U4.15 (~OE), U6.2, U6.11
~IOR: J3.14 (~IOR), U5.3
~IOW: J3.13 (~IOW), U5.5
~MIDI_DRV: U5.2, U10.4; also elsewhere on the board
~RDACK: U1.25 (GPIO19), U5.10
~RIOR: U1.7 (GPIO5), U6.8
~RIOW: U1.6 (GPIO4), U6.6
~RI/OCHRDY: R18.1, U1.31 (GPIO26_ADC0), U10.1
~SPI_CS: U1.2 (GPIO1), U8.1 (~CE)

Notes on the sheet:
Saves PIO instructions due to JMP limitations
DECOUPLING CAPS
I2S DAC
Disables ~{IOR} and ~{IOW} signals when other DMA in system happens
Latches ~{BUSOE} low after ADS is toggled for the first time, sets high on RESET
MIDI/DEBUG OUT
MOUNTING
MISC LEVEL SHIFT/BUFFER
IRQ/DMA SETTING
DACK INVERT
ADDR/DATA MUX/DEMUX
SAMPLE RAM
AEN IO MASKING
ISA AND RASPBERRY PI PICO
RESET CIRCUIT
I/OCHRDY OPEN DRAIN
74xx LOGIC PWR
U10 = 74AHCT126 @ +5V (TTL inputs take 3V3 logic) Pseudo open-drain: A=GND, OE=1 -> low, OE=0 -> Hi-Z Gates C/D + power unit: "Wavetable & line out" sheet
THT board v1.3.2: the GY-PCM5102 module option (v1.2 I2S_DAC1/J4, v1.3.0/v1.3.1 J10) is gone: U9 (TSSOP-20, on the card) is the DAC.
THT board: J2 (ISA debug header, never fitted) is removed - its pads blocked the ISA routing.

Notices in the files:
hw-tht-v1.3/PicoGUS-THT.kicad_pcb:
© 2023-2026 Ian Scott (polpo), Vidar Waagbø (waagbo)
Licensed under CERN-OHL-P v2
